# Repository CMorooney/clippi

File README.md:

# LZX/Eurorack compatible video clip player

# Features
- Store up to 12 banks of 12 clips via web interface
  - upload local videos or provide youtube links
  - re-order and rename clips
- Visualize current clip playback % with neopixel ring
- Visualize current bank/clip with a 7 segment display
- Random/Sequential playback modes
- 'Hold' current clip mode
- All buttons/features can also be invoked with voltage triggers

# How to use
- clone repo onto RPi
- install python3 and set up virtual python env
- install [pexpect](https://pexpect.readthedocs.io/en/stable/install.html)
- install [mplayer](http://www.mplayerhq.hu/design7/dload.html)
- create alias for running python scripts with `sudo` and passing env variables to the virtual env
  - `alias supy='sudo -E env PATH=$PATH python3
- added this line to `/boot/config.txt`
  - `dtoverlay=gpio-shutdown,gpio_pin=21`
- create/enable system services to start web-app and clip player so they start on boot
- create `.env` file at repo root
- reboot pi, web app should be at http://clippi.local:5000/ once that's complete

player.service (the actual clip looper):
```
[Unit]
Description=clippi.player

[Service]
User=calvin
ExecStart=sudo -E env PATH=$PATH /home/calvin/env/bin/python3 /home/calvin/App/app.py
StartLimitIntervalSec=8
StartLimitBurst=1
Restart=always

[Install]
WantedBy=multi-user.target
```

app.service (the web-app):
```
[Unit]
Description=clippi

[Service]
ExecStart=/home/calvin/env/bin/python3 /home/calvin/App/web/RaspWebInterface.py
Restart=always

[Install]
WantedBy=default.target
```

I more/less followed instructions [here](https://www.makeuseof.com/what-is-systemd-launch-programs-raspberry-pi/)
to set up the system services

the content in the `.env` file you created should look like this:
```
WEB_APP_SECRET_KEY=your_secret_key
BANK_COUNT=number
BANK_SIZE=number
APP_PATH=path_to_root_of_application
BANKS_PATH=path_to_banks
```

for my working prototype the values (outside of the secret, lol) are:
```
BANK_COUNT=12
BANK_SIZE=12
APP_PATH='/home/calvin/App'
BANKS_PATH='/home/calvin/App/__CONTENT'
```

theoretically they should be able to be defined as whatever but the .gitignore importantly include the `__CONTENT` directory that is my BANKS_PATH. An important but unenforced coupling so just make sure whatever you use as your BANKS_PATH is in your .gitignore
`consoleblank=1 vt.global_cursor_default=0` was appended to `/boot/cmdline.txt` to remove boot splash image and console/cursor

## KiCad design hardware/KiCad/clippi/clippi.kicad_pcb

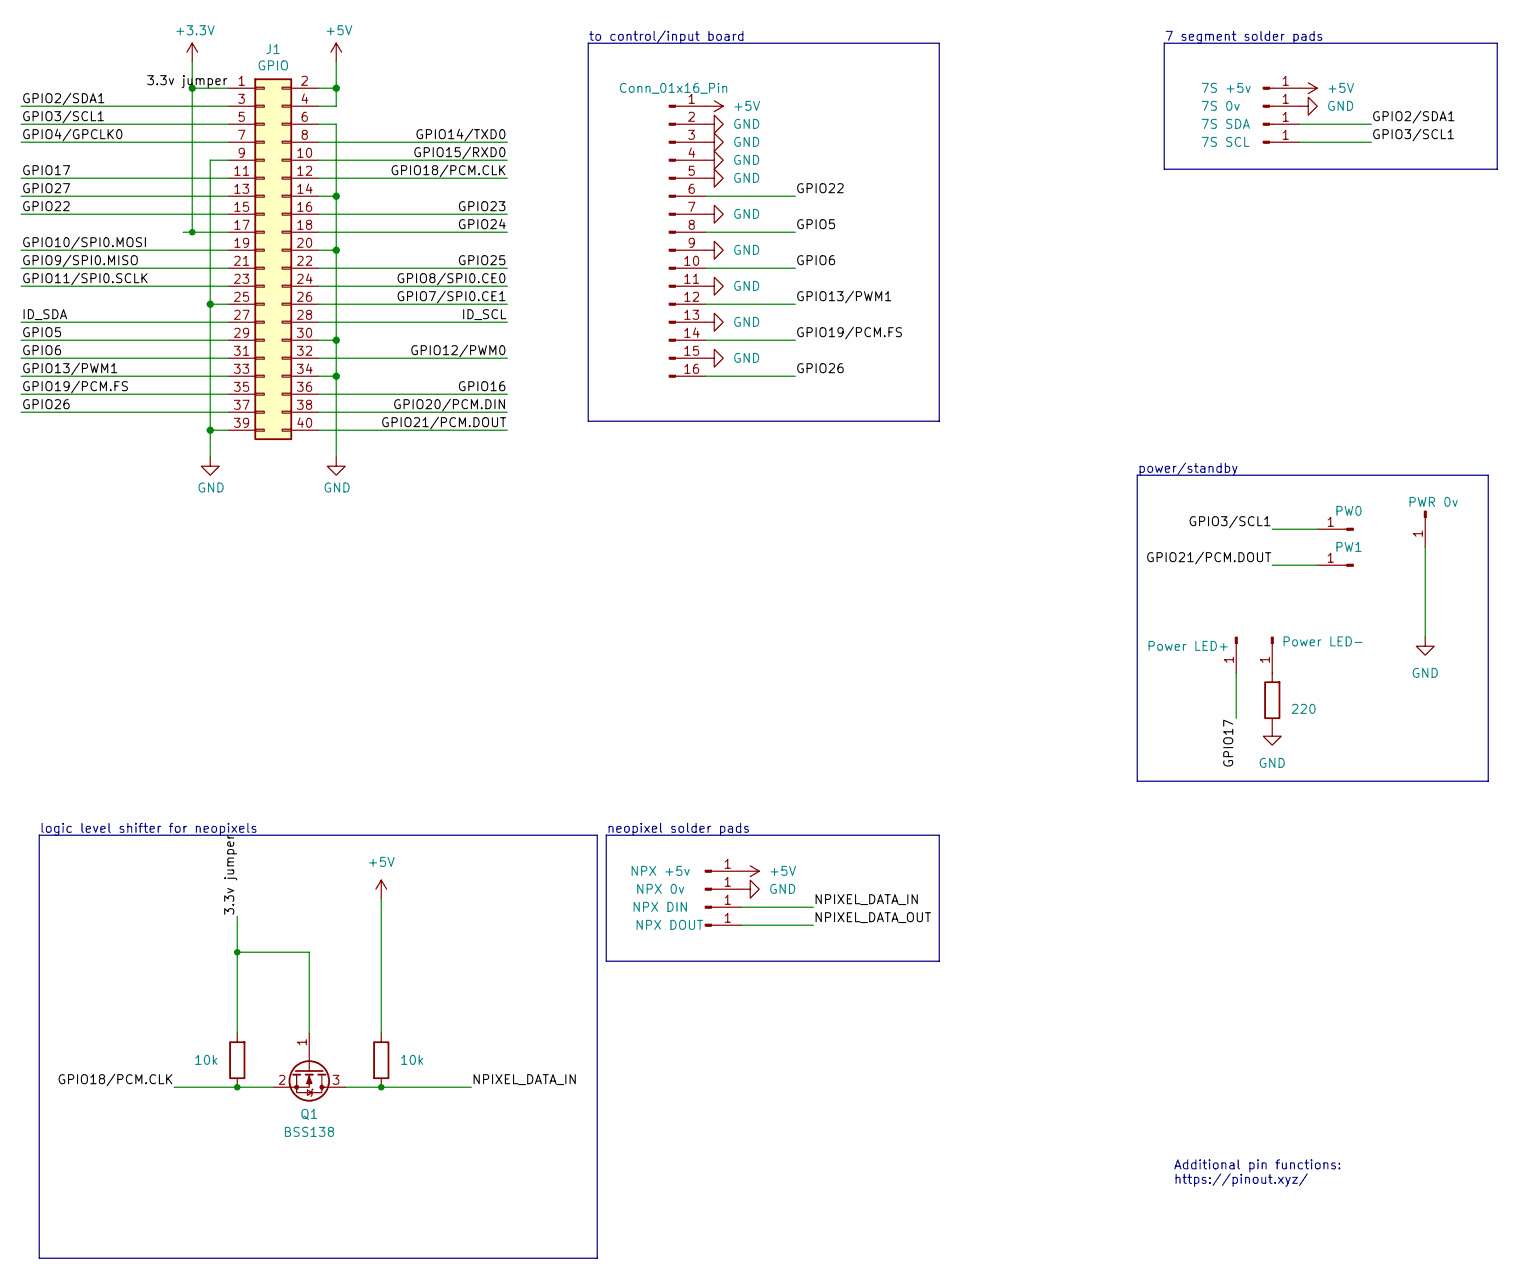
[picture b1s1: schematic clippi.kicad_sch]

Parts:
0v1: NPX 0v; TestPoint_THTPad_2.0x2.0mm_Drill1.0mm
0v2: 7S 0v; TestPoint_THTPad_2.0x2.0mm_Drill1.0mm
5v1: 7S +5v; TestPoint_THTPad_2.0x2.0mm_Drill1.0mm
+5v1: NPX +5v; TestPoint_THTPad_2.0x2.0mm_Drill1.0mm
DIN1: NPX DIN; TestPoint_THTPad_2.0x2.0mm_Drill1.0mm
DOUT1: NPX DOUT; TestPoint_THTPad_2.0x2.0mm_Drill1.0mm
J1: GPIO; PinSocket_2x20_P2.54mm_Vertical
J2: Conn_01x16_Pin; IDC-Header_2x08_P2.54mm_Vertical
PW0: PW0; TestPoint_THTPad_2.0x2.0mm_Drill1.0mm
PW1: PW1; TestPoint_THTPad_2.0x2.0mm_Drill1.0mm
PWR_0v1: PWR 0v; TestPoint_THTPad_2.0x2.0mm_Drill1.0mm
PW_LED+1: Power LED+; TestPoint_THTPad_2.0x2.0mm_Drill1.0mm
PW_LED-1: Power LED-; TestPoint_THTPad_2.0x2.0mm_Drill1.0mm
Q1: BSS138; SOT-23
R3, R4: 10k; R_Axial_DIN0204_L3.6mm_D1.6mm_P7.62mm_Horizontal
R5: 220; R_Axial_DIN0204_L3.6mm_D1.6mm_P7.62mm_Horizontal
SCL1: 7S SCL; TestPoint_THTPad_2.0x2.0mm_Drill1.0mm
SDA1: 7S SDA; TestPoint_THTPad_2.0x2.0mm_Drill1.0mm

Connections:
+3V3: J1.1, J1.17, Q1.1 (G), R3.2
+5V: 5v1.1, +5v1.1, J1.2, J1.4, J2.1, R4.1
/GPIO2/SDA1: J1.3, SDA1.1
/GPIO3/SCL1: J1.5, PW0.1, SCL1.1
/GPIO4/GPCLK0: J1.7
/GPIO5: J1.29, J2.8
/GPIO6: J1.31, J2.10
/GPIO7/SPI0.CE1: J1.26
/GPIO8/SPI0.CE0: J1.24
/GPIO9/SPI0.MISO: J1.21
/GPIO10/SPI0.MOSI: J1.19
/GPIO11/SPI0.SCLK: J1.23
/GPIO12/PWM0: J1.32
/GPIO13/PWM1: J1.33, J2.12
/GPIO14/TXD0: J1.8
/GPIO15/RXD0: J1.10
/GPIO16: J1.36
/GPIO17: J1.11, PW_LED+1.1
/GPIO18/PCM.CLK: J1.12, Q1.2 (S), R3.1
/GPIO19/PCM.FS: J1.35, J2.14
/GPIO20/PCM.DIN: J1.38
/GPIO21/PCM.DOUT: J1.40, PW1.1
/GPIO22: J1.15, J2.6
/GPIO23: J1.16
/GPIO24: J1.18
/GPIO25: J1.22
/GPIO26: J1.37, J2.16
/GPIO27: J1.13
/ID_SCL: J1.28
/ID_SDA: J1.27
/NPIXEL_DATA_IN: DIN1.1, Q1.3 (D), R4.2
/NPIXEL_DATA_OUT: DOUT1.1
GND: 0v1.1, 0v2.1, J1.6, J1.9, J1.14, J1.20, J1.25, J1.30, J1.34, J1.39, J2.2, J2.3, J2.4, J2.5, J2.7, J2.9, J2.11, J2.13, J2.15, PWR_0v1.1, R5.1
unnamed: PW_LED-1.1, R5.2

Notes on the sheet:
Additional pin functions: https://pinout.xyz/
7 segment solder pads
power/standby
logic level shifter for neopixels
neopixel solder pads
to control/input board

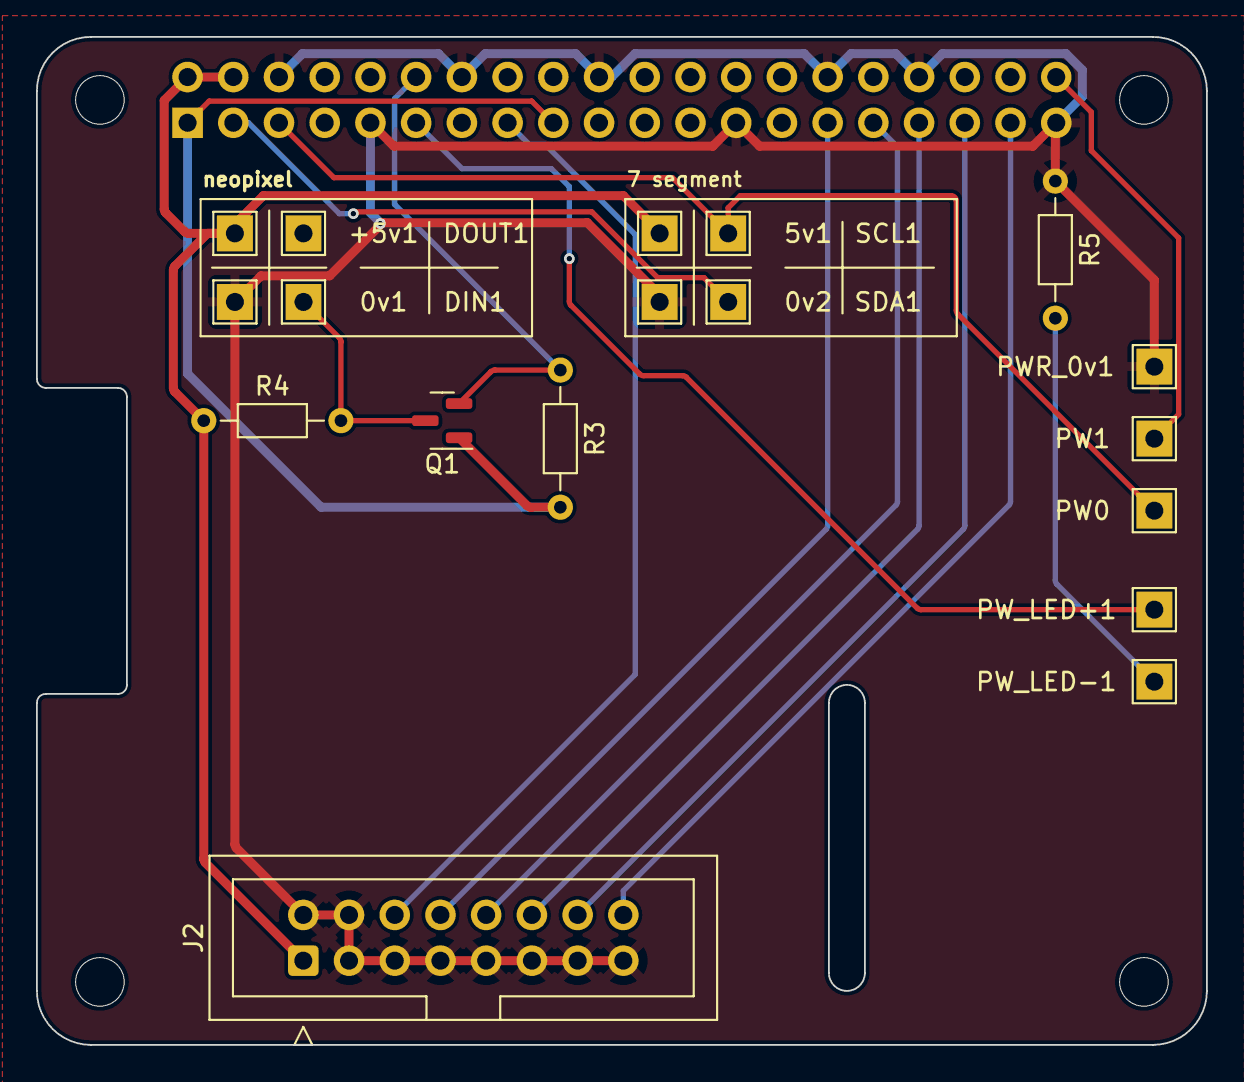
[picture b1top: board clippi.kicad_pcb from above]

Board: 2 copper layers, 65.0 x 56.0 mm, 23 parts (1 on the bottom side), 16 nets.

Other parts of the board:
MH1, MH2, MH3, MH4: MountingHole_2.7mm_M2.5

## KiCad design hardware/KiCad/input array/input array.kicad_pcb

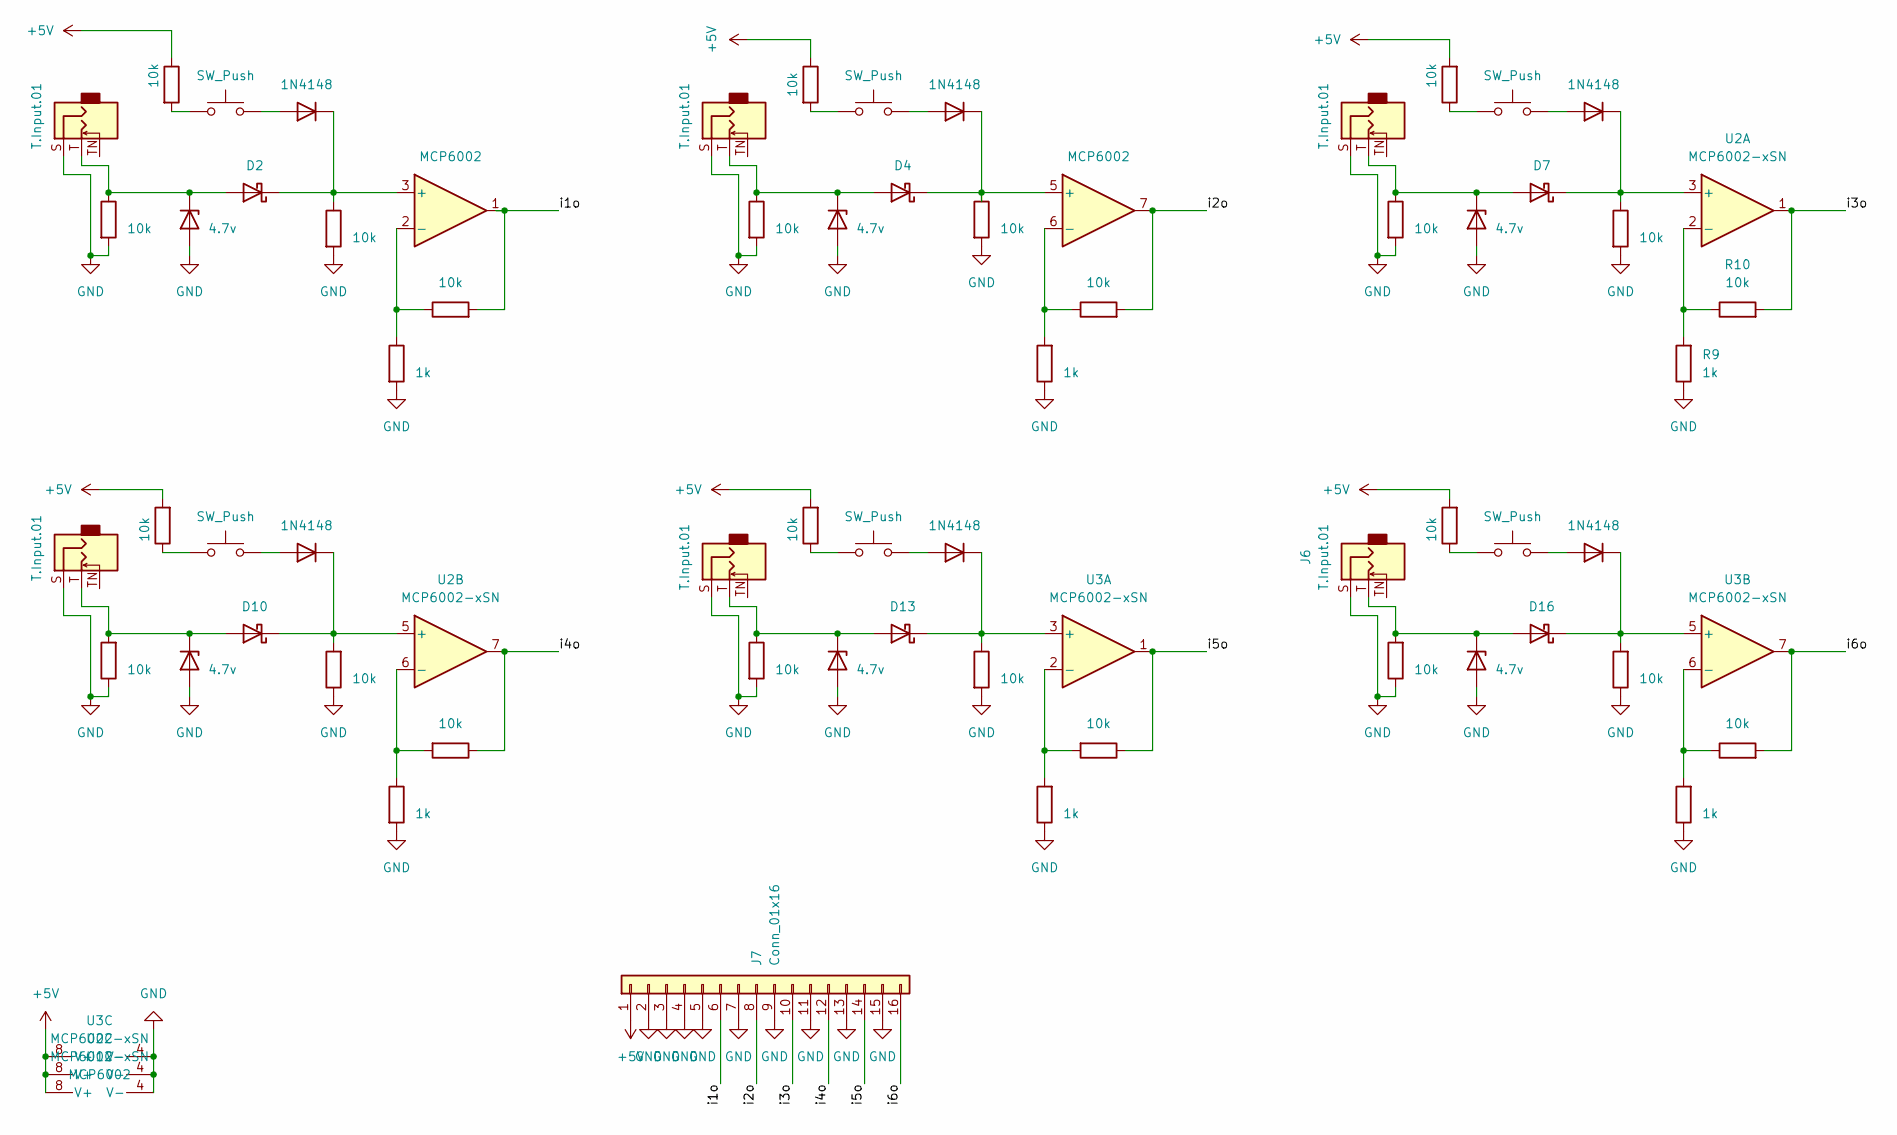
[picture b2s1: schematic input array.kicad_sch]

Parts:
D1, D3, D6, D9, D12, D15: 4.7v; D_DO-41_SOD81_P7.62mm_Horizontal
D2, D4, D7, D10, D13, D16: D_DO-15_P10.16mm_Horizontal
D5, D8, D11, D14, D17, D20: 1N4148; D_DO-35_SOD27_P7.62mm_Horizontal
J1, J2, J3, J4, J5, J6: T.Input.01; Jack_3.5mm_QingPu_WQP-PJ398SM_Vertical_CircularHoles
J7: Conn_01x16; IDC-Header_2x08_P2.54mm_Vertical
R1, R2, R3, R5, R6, R7, R10, R11, R12, R13, R14, R15, R18, R19, R20, R22, R23, R24, R25, R26, R27, R29, R30: 10k; R_Axial_DIN0204_L3.6mm_D1.6mm_P5.08mm_Horizontal
R4, R8, R9, R16, R17, R21: 1k; R_Axial_DIN0204_L3.6mm_D1.6mm_P5.08mm_Horizontal
R28: 10k; R_Axial_DIN0204_L3.6mm_D1.6mm_P5.08mm_Vertical
SW1, SW2, SW3, SW4, SW5, SW6: SW_Push; SW_Cherry_MX_1.00u_PCB
U1: MCP6002; DIP-8_W7.62mm_Socket
U2, U3: MCP6002-xSN; DIP-8_W7.62mm_Socket

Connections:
+5V: J7.1, R25.1, R26.1, R27.2, R28.2, R29.2, R30.2, U1.8 (V+), U2.8 (V+), U3.8 (V+)
/i1o: J7.6, R3.2, U1.1
/i2o: J7.8, R7.2, U1.7
/i3o: J7.10, R10.2, U2.1
/i4o: J7.12, R22.1, U2.7
/i5o: J7.14, R18.1, U3.1
/i6o: J7.16, R13.2, U3.7
GND: D1.2 (A), D3.2 (A), D6.2 (A), D9.2 (A), D12.2 (A), D15.2 (A), J1.S, J2.S, J3.S, J4.S, J5.S, J6.S, J7.2, J7.3, J7.4, J7.5, J7.7, J7.9, J7.11, J7.13, J7.15, R1.2, R2.2, R4.2, R5.2, R6.2, R8.1, R9.1, R11.2, R12.2, R14.1, R15.1, R16.1, R17.1, R19.2, R20.2, R21.2, R23.1, R24.1, U1.4 (V-), U2.4 (V-), U3.4 (V-)
unnamed: D1.1 (K), D2.2 (A), J1.T, R1.1
unnamed: D2.1 (K), D20.1 (K), R2.1, U1.3 (+)
unnamed: D3.1 (K), D4.2 (A), J2.T, R5.1
unnamed: D4.1 (K), D5.1 (K), R6.1, U1.5 (+)
unnamed: D5.2 (A), SW2.2
unnamed: D6.1 (K), D7.2 (A), J3.T, R11.1
unnamed: D7.1 (K), D8.1 (K), R12.1, U2.3 (+)
unnamed: D8.2 (A), SW3.2
unnamed: D9.1 (K), D10.2 (A), J4.T, R24.2
unnamed: D10.1 (K), D11.1 (K), R23.2, U2.5 (+)
unnamed: D11.2 (A), SW4.2
unnamed: D12.1 (K), D13.2 (A), J5.T, R20.1
unnamed: D13.1 (K), D14.1 (K), R19.1, U3.3 (+)
unnamed: D14.2 (A), SW5.2
unnamed: D15.1 (K), D16.2 (A), J6.T, R15.2
unnamed: D16.1 (K), D17.1 (K), R14.2, U3.5 (+)
unnamed: D17.2 (A), SW6.2
unnamed: D20.2 (A), SW1.2
unnamed: R25.2, SW1.1
unnamed: R26.2, SW2.1
unnamed: R27.1, SW3.1
unnamed: R28.1, SW6.1
unnamed: R29.1, SW5.1
unnamed: R30.1, SW4.1
unnamed: R3.1, R4.1, U1.2 (-)
unnamed: R7.1, R8.2, U1.6 (-)
unnamed: R9.2, R10.1, U2.2 (-)
unnamed: R21.1, R22.2, U2.6 (-)
unnamed: R17.2, R18.2, U3.2 (-)
unnamed: R13.1, R16.2, U3.6 (-)

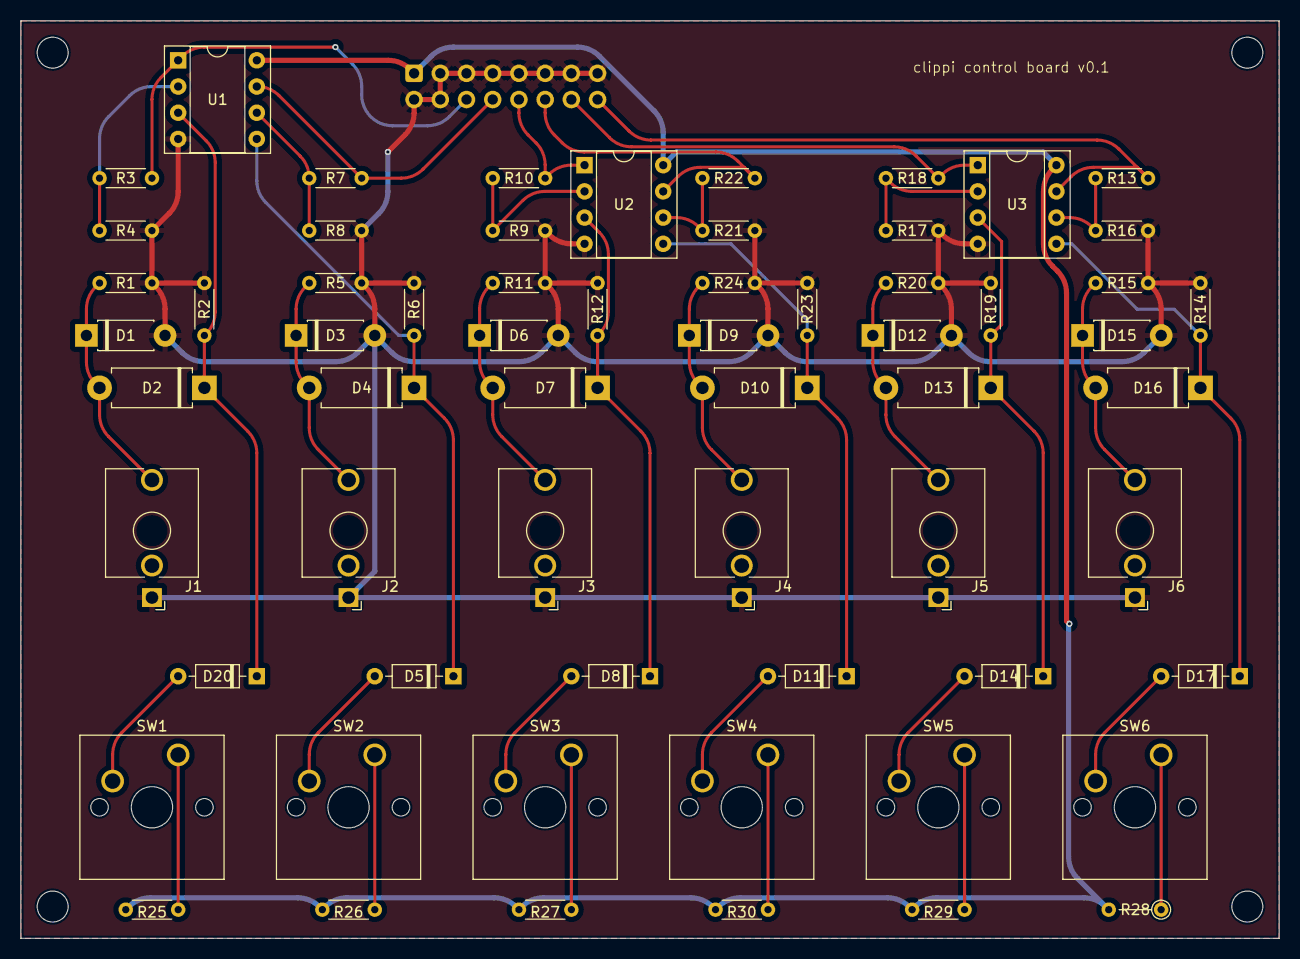
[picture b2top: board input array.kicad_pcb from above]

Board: 2 copper layers, 121.9 x 88.9 mm, 64 parts (1 on the bottom side), 38 nets.

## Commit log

2023-12-09 initial
2023-12-09 adds simple readme
2023-12-09 basic mp4 upload and listing of files on bank 01 on web interface
2023-12-09 reads app_scret for web app from .env file (ignored in version control)
2023-12-09 basic file delete
2023-12-09 when running actual app, ensure the bank directories exist
2023-12-09 display files per-bank on web interface. not very testable as you can't upload to a specific bank yet
2023-12-09 adds bank-selection in web interface for file upload, allowing user to select which bank to upload to, not enabling them to go over the max defined in the env vars
2023-12-09 adds .env info to readme for when I forget
2023-12-09 fix delete for banks that aren't 01
2023-12-09 ugly, but put flash() back
2023-12-09 better redirects after upload/delete in web interface
2023-12-09 adds more notes about startup services now that the clip-player script is starting on boot and the web start depends on it
2023-12-10 adds youtube upload options, style and javacsript for some usefuleness
2023-12-10 loading indicator for uploading
2023-12-10 save/display videos with their bank number in the file name. quickest/easiest/sloppiest way to handle ordering
2023-12-10 adds basic rename function. still needs some kind of sanitation I'm sure the wrong input could really fucks u up
2023-12-10 move clips up/down within bank
2023-12-10 sanitize uploaded slip names
2023-12-10 sanitize in more places just in case
2023-12-10 youtube start/end time
2023-12-10 basic styling using color palette https://lospec.com/palette-list/cc-29 and nerdfont ProFont
2023-12-11 main app boot LED status
2023-12-11 a little readme dump for a change I made outside of the repo for power off switch
2023-12-17 status led tests
2023-12-17 rewrite app.py to use GPIO interrupt&edge detection/threaded callbacks
2023-12-19 fix cpu overheating lol. use pexpect to spawn mplayer process in slave mode
2023-12-20 specific mplayer path to help with systemd
2023-12-20 adds README chunk for the way I disabled boot logo/console/cursor
2023-12-20 command queue and showing current clip progress on neopixel
2023-12-20 play playlist of everything in the first bank. implement next/previous buttons
2023-12-20 pixel progress cleanup
2023-12-20 better/more comments in main app file. inits 7 segment display and sets clip # to appropriate digits
2023-12-21 some code formatting but also start putting shift functionality in and show colon on 7 segment display
2023-12-21 global/file scope variable for current and pending bank. working with shift button and 7-segment display up until shift is released and mplayer actually needs to do something
2023-12-21 remove debounce for shift key. encapsulate set_files and use less escape characters for playlist/file loading
2023-12-24 buttons to active high so I can OR with external triggers easily
2023-12-24 adds cleanup so machine doesn't always show what it was last doing if service/app dies or is powered off
2024-01-08 adds kicad files for control board and pi hat. adds to gitignore for kicad stuff
2024-01-17 add gerber zip to gitignore
2024-01-17 re-lay out the pi hat, re-trace, add copper fill, and I generated gerber files and set it off to PCB way
2024-01-24 adds blender project and some gitignore entries to try and keep it clean. pretty close to SOME kind of fully working/assemblable enclosure
2024-01-25 more blender enclosure v1 adjustments
2024-01-25 adds references to main app dependencies so I can close some browser tabs
2024-01-31 organizes blender directory a little so it's easier to find the models for individual parts that I have been using for reference when designing/modeling enclosures. adds first pass at much improved v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
2024-02-01 another pass at v2 of enclosure, minor adjustments mostly
2024-02-04 v2 model cone
2024-02-04 fix pi hat board/schematic to ensure 3.3v is supplied to the logic shifter, that got missed
2024-02-04 hardware/peripheral test script adjustments
2024-02-04 fix power led pin for the acual board
2024-02-04 cut neopixel brightness down significantly. still so bright
2024-02-05 implements random/sequential mode -- shows progress neopixels as red when random mode is on
2024-02-05 comment and code cleanup, reduce button debouncing now that we're using nicer switches on the actual device
2024-02-05 persists 'hold' 'random' modes and selected bank to file system
2024-02-05 adds more parts to the blender project so that I can take some screen grabs with the keycaps on and stuff
2024-02-05 adds some images/screen grabs to use later for readme and b.log post
2024-02-05 smaller images sheesh
2024-02-05 rename
2024-02-05 adds web interface screen grab
